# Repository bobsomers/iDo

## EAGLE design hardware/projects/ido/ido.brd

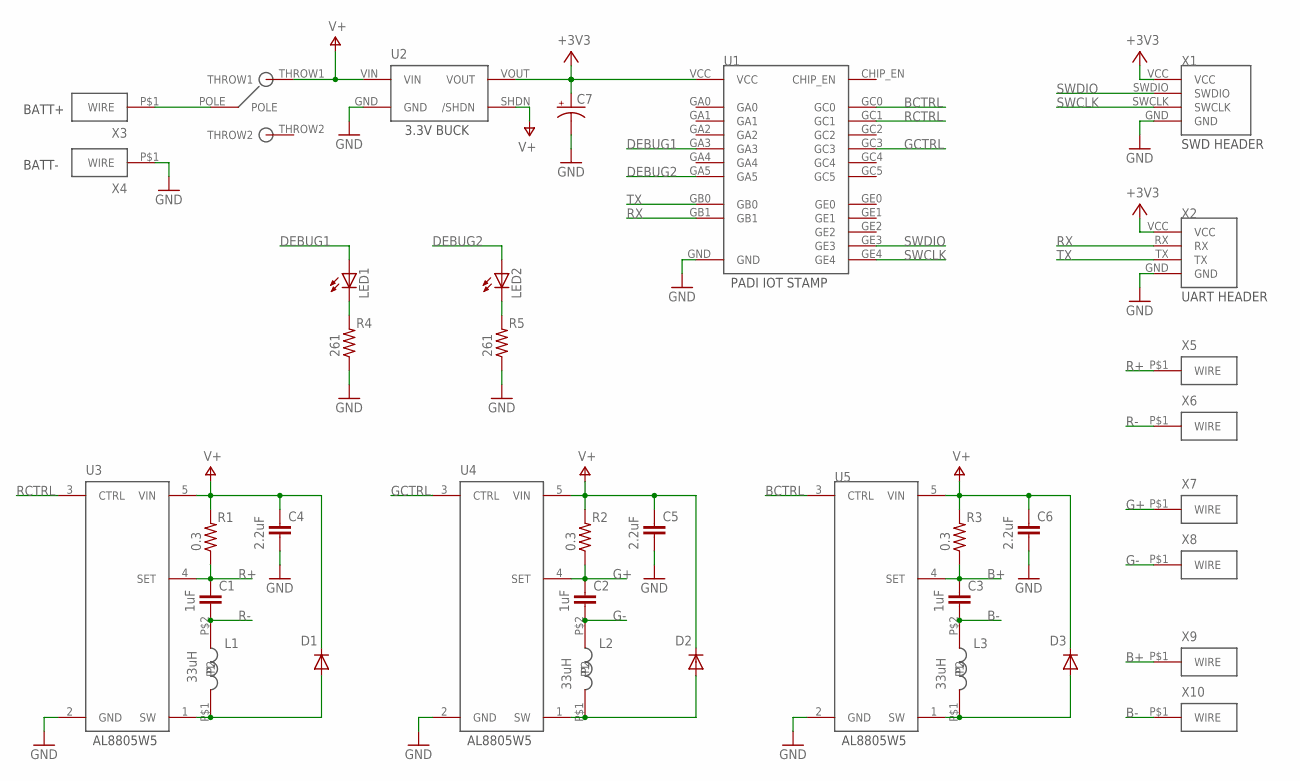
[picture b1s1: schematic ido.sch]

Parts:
C1, C2, C3: 1uF; C0603
C4, C5, C6: 2.2uF; C0603
C7: CPOL-USE2.5-7; E2,5-7
D1, D2, D3: DIODE-DO214AC; DO214AC
L1, L2, L3: 33uH; MURATA-INDUCTOR
LED1, LED2: LEDCHIPLED_0603; CHIPLED_0603
R1, R2, R3: 0.3; R0603
R4, R5: 261; R0603
S1: SLIDE-SWITCH
U1: PADI-IOT-STAMP
U2: POLOLU-BUCK
U3, U4, U5: AL8805W5; SOT25
X1: PROGRAMMING-HEADER
X2: UART-HEADER
X3, X4, X5, X6, X7, X8, X9, X10: WIRE-HOLE

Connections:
+3V3: C7.+, U1.VCC, U2.VOUT, X1.VCC, X2.VCC
B+: C3.1, R3.1, U5.4 (SET), X9.P$1
B-: C3.2, L3.P$2 (P2), X10.P$1
BCTRL: U1.GC0, U5.3 (CTRL)
DEBUG1: LED1.A, U1.GA3
DEBUG2: LED2.A, U1.GA5
G+: C2.1, R2.1, U4.4 (SET), X7.P$1
G-: C2.2, L2.P$2 (P2), X8.P$1
GCTRL: U1.GC3, U4.3 (CTRL)
GND: C4.2, C5.2, C6.2, C7.-, R4.1, R5.1, U1.GND, U2.GND, U3.2 (GND), U4.2 (GND), U5.2 (GND), X1.GND, X2.GND, X4.P$1
unnamed: S1.POLE, X3.P$1
unnamed: LED2.C, R5.2
unnamed: D1.A, L1.P$1 (P1), U3.1 (SW)
unnamed: LED1.C, R4.2
unnamed: D2.A, L2.P$1 (P1), U4.1 (SW)
unnamed: D3.A, L3.P$1 (P1), U5.1 (SW)
R+: C1.1, R1.1, U3.4 (SET), X5.P$1
R-: C1.2, L1.P$2 (P2), X6.P$1
RCTRL: U1.GC1, U3.3 (CTRL)
RX: U1.GB1, X2.RX
SWCLK: U1.GE4, X1.SWCLK
SWDIO: U1.GE3, X1.SWDIO
TX: U1.GB0, X2.TX
V+: C4.1, C5.1, C6.1, D1.C, D2.C, D3.C, R1.2, R2.2, R3.2, S1.THROW1, U2.SHDN (/SHDN), U2.VIN, U3.5 (VIN), U4.5 (VIN), U5.5 (VIN)

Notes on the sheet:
BATT+
BATT-

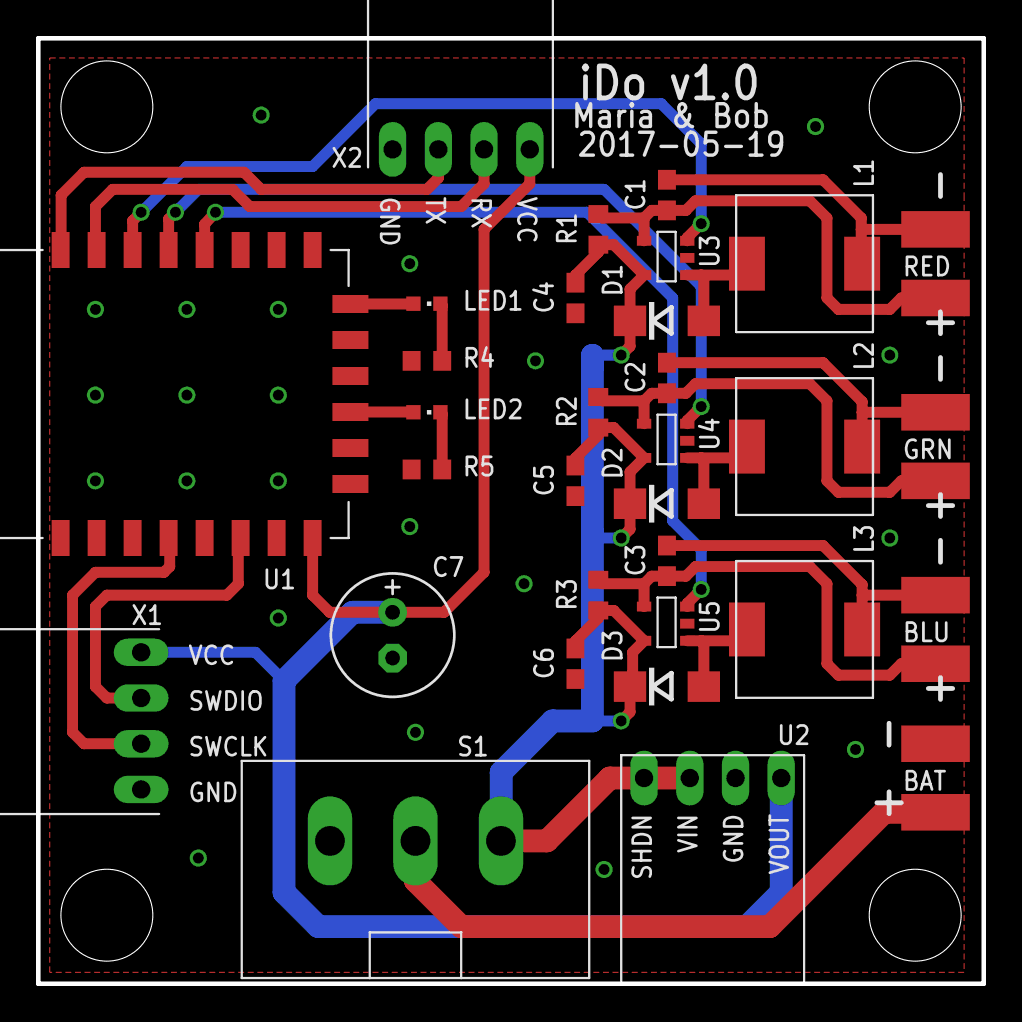
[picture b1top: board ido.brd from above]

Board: 2 copper layers, 52.5 x 52.5 mm, 36 parts (0 on the bottom side), 24 nets.

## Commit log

2017-02-28 Playing around with RGB LEDs.
2017-02-28 Decent Makefile going on...
2017-02-28 Does a thing.
2017-02-28 Smoother graphics now that GLFW owns the main loop.
2017-03-14 WIP.
2017-03-14 Initial import of RTL8710 SDK project.
2017-03-14 Leave src in SDK directory, copy here to save.
2017-03-14 Firmware gitignore.
2017-03-14 PWM working.
2017-03-14 Moved to FreeRTOS task.
2017-03-21 Add iDo schematic WIP.
2017-03-21 Cycle colors.
2017-03-21 Add parts library and OSH Park DRU.
2017-03-21 Adding datasheets for parts.
2017-03-23 Adding heatsink datasheet.
2017-03-23 Added debug LEDs.
2017-03-23 Preliminary board placement.
2017-03-24 Board and hole dimensions set and layout WIP.
2017-03-28 Final board rev.
2017-03-30 Move diodes down a bit to make assembly easier.
2017-04-16 WIP firmware on production boards.
2017-04-26 Turn on optimizations.
2017-04-28 Some refactoring.
2017-04-28 Effect selector and some simple effects.
2017-05-13 Sinks.
2017-05-13 Hook up checkboxes to sinks.
2017-05-14 Tables.
2017-05-14 Lights, colors not hooked up yet.
2017-05-14 Light visualizer hooked up!
2017-05-14 Network sink to UDP broadcast port 12345.
2017-05-14 Firmware test mode.
2017-05-14 Status LEDs task.
2017-05-15 Auto-connecting to Wi-Fi network!
2017-05-15 Working firmware.
2017-05-15 Limit packet rate to 10 Hz.
2017-05-17 Added portaudio submodule. Updated makefile to build and include portaudio
2017-05-17 Added static AudioDevice class which includes initialization and callback functions. Confirmed input appears to work
2017-05-19 Fixed FFTW and had it output semi-sane sound spectrums
2017-05-19 Moved spectrum effect into audio_effect.cpp
2017-05-19 Added ring buffer for audio. Added fftw to build process. Tried (and failed) to add FFT calls... seems to be causing a segfault when uncommented
2017-05-19 Fade stuff.
2017-05-19 Cycle effect.
2017-05-19 Chase effect.
2017-05-19 Added color gradient to the resulting spectrum in AudioEffect
2017-05-19 Fix cycle effect.
